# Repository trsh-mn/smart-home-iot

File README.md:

# 스마트홈 IoT 시스템

라즈베리파이 5를 두뇌로, **AI 음성대화봇 · 음악 스피커 · 스마트 전등** 세 기기가 하나의 시스템으로 동작합니다.
무거운 판단(음성인식 · LLM · TTS)은 Pi가, 입출력은 각 기기의 ESP32가 맡도록 역할을 나눴습니다.

## 시스템 구성

```mermaid
flowchart TB
    PI["<b>Raspberry Pi 5</b><br/>Gemini · edge-tts · mosquitto(MQTT)"]
    BOT["<b>AI 음성대화봇</b><br/>ESP32-WROOM-32E"]
    SPK["<b>음악 스피커</b><br/>ESP32-WROOM-32E"]
    LAMP["<b>스마트 전등</b><br/>ESP32-C3"]
    PHONE["휴대폰"]

    BOT -- "UDP 5005 · 마이크 PCM" --> PI
    PI -- "UDP 6000 · 음성 응답 PCM" --> BOT
    PI -- "TCP 6001 · 음악 스트림" --> SPK
    PHONE -. "Bluetooth A2DP" .-> SPK
    PI -- "MQTT · 전원/색상/밝기" --> LAMP
    PI <-- "MQTT · 상태 · 볼륨" --> BOT
    PI <-- "MQTT · 모드 · 볼륨" --> SPK
```

| 데이터 | 방식 | 이유 |
|---|---|---|
| 상태 전환 · 제어 명령 | **MQTT** | 작고 가벼운 메시지 |
| 짧은 음성 (마이크 · 응답) | **UDP** | 지연이 적음 |
| 긴 음악 스트림 | **TCP** | 손실 없이 순서 보장 |

## 폴더 구조

```
firmware/
├── voice_bot/       AI 음성대화봇 (Arduino)
├── music_speaker/   Wi-Fi · Bluetooth 음악 스피커 (Arduino)
└── smart_lamp/      스마트 전등 (ESP-IDF)
server/              라즈베리파이 코드 (Python)
hardware/
├── lamp_v1/         전등 PCB v1 — KiCad 원본, 거버, BOM, CPL
└── lamp_v2/         전등 PCB v2 (진행 중) — KiCad 원본
docs/images/         사진 · 회로도 · PCB 이미지
```

---

## 1. AI 음성대화봇 — `firmware/voice_bot`

- ESP32는 마이크 · 스피커 입출력만, Pi는 음성인식 · LLM · TTS를 담당
- 상태(`idle` · `listening` · `thinking` · `speaking` · `playing_music`)는 MQTT, 음성은 **16-bit / 16kHz mono PCM**을 UDP로 전송
- **RMS 기반 VAD**로 말할 때만 전송. 음악이 재생 중이면 역치를 높여 음악 소리를 무시
- 응답 재생 중(+300ms)에는 녹음하지 않아 자기 목소리를 명령으로 인식하지 않음

| 부품 | 연결 (ESP32 GPIO) |
|---|---|
| INMP441 마이크 (I2S) | SCK 32 · WS 33 · SD 34 |
| MAX98357A 앰프 (I2S) | BCLK 26 · LRC 25 · DIN 22 |
| 스피커 | 8Ω 3W |

## 2. Wi-Fi · Bluetooth 음악 스피커 — `firmware/music_speaker`

- 대화 응답과 음악이 한 스피커에서 충돌하지 않도록 **기기를 분리**
- **Wi-Fi 모드**: Pi의 음악을 TCP로 수신 (44.1kHz 스테레오) / **Bluetooth 모드**: 휴대폰과 직접 연결
- 모드 전환: BOOT 버튼 1초 또는 MQTT `music/mode` ← `bt` / `wifi`

| 부품 | 연결 (ESP32 GPIO) |
|---|---|
| MAX98357A 앰프 (I2S) | BCLK 26 · LRC 25 · DIN 22 |
| 모드 전환 버튼 | BOOT (GPIO 0) |

## 3. 스마트 전등 — `firmware/smart_lamp`

- 18650 배터리로 동작하는 무선 전등. **PCB를 KiCad로 직접 설계**하고 JLCPCB에서 제작
- Arduino → **ESP-IDF**로 이전, MQTT 토픽 세 개로 전원 · 색상 · 밝기 제어
- 제어 함수를 Pi 쪽 `server/lamp/core.py`로 모아 Gemini · 알람 · (향후) 앱이 같은 함수를 호출
- 원하는 시간에 켜고 끄는 알람 예약 (APScheduler, cron 방식)

| 항목 | 내용 |
|---|---|
| MCU | ESP32-C3 |
| LED | WS2812B 30구 · GPIO 4 · RMT 제어 |
| 전원 | 18650 셀 · 5V 부스트 |
| 레벨 시프터 | 74AHCT125 (3.3V → 5V) |

### PCB v1 → v2

| | v1 (제작 완료) | v2 (아트웍 진행 중) |
|---|---|---|
| PCB |  |  |
| MCU | 개발보드를 꽂아서 사용 | ESP32-C3-WROOM-02 모듈 직접 실장 |
| 전원 | 외부 부스트 모듈 사용 | 충전(TP4056) · 부스트(MT3608) · LDO(ME6211) 내장 |
| 레벨 시프터 | 74AHCT125 (4채널) | 74AHCT1G125 (1채널) |
| LED 전원 | 항상 공급 | 로드 스위치(TPS22919)로 펌웨어가 켜고 끔 |
| 펌웨어 업로드 | 개발보드 USB | ESP32-C3 내장 USB (USB-C) |

회로도: [v1](docs/images/lamp_v1_schematic.png) · [v2](docs/images/lamp_v2_schematic.png)

---

## MQTT 토픽

| 토픽 | 값 | 보내는 쪽 → 받는 쪽 |
|---|---|---|
| `lamp/power` | `on` / `off` | Pi → 전등 |
| `lamp/brightness` | `0` ~ `100` | Pi → 전등 |
| `lamp/color` | `[r, g, b]` 또는 `r,g,b` | Pi → 전등 |
| `device/state` | `idle` / `thinking` / `speaking` … | Pi → |
| `music/state` | `playing` / `stopped` | Pi → 음성대화봇 (VAD 역치 조절) |
| `speaker/volume` | `0` ~ `100` | → 음성대화봇 |
| `music/volume` | `0` ~ `100` | → 음악 스피커 |
| `music/mode` | `bt` / `wifi` | → 음악 스피커 |

---

## 트러블슈팅

### 마이크에 잡음만 들어오는 문제 (음성대화봇)
- **문제**: 한 보드에 마이크와 스피커(앰프)를 함께 배선하자 마이크 입력에 "지지직" 잡음만 들어옴
- **확인**: 멀티미터로 각 부품의 전압을 측정하며 하나씩 정상 동작을 확인
- **해결**: 마이크와 스피커(앰프)의 GND 선을 분리해 연결 → 잡음 해결

### Wi-Fi · Bluetooth 동시 사용 시 용량 부족 (음악 스피커)
- **문제**: Wi-Fi와 Bluetooth 오디오를 동시에 쓰기엔 ESP32의 용량이 부족
- **해결**: 두 모드로 나누고, Bluetooth 사용 중에는 Wi-Fi 오디오를 끄도록 전환 설계

### ESP32-C3는 클래식 Bluetooth 미지원 (음악 스피커)
- **문제**: 휴대폰 음악을 받으려면 클래식 Bluetooth(A2DP)가 필요한데 ESP32-C3는 미지원
- **해결**: 클래식 Bluetooth를 지원하는 ESP32-WROOM-32E 선택

### ESP-IDF 전환 후 Wi-Fi 연결 실패 (스마트 전등)
- **문제**: Arduino에서는 잘 되던 Wi-Fi가 ESP-IDF로 옮기자 연결 실패 (인증 타임아웃)
- **확인**: ESP32-C3 저가 보드에서 송신(TX) 출력이 너무 강해 같은 문제가 생기는 사례 확인
- **해결**: 송신 출력을 낮춰 연결 안정화 (34 × 0.25dBm = 8.5dBm)
  ```c
  ESP_ERROR_CHECK(esp_wifi_set_max_tx_power(34));
  ```

---

## 빌드 · 실행

### 공통: 비밀 정보 설정
Wi-Fi · MQTT 계정과 API 키는 GitHub에 올리지 않습니다. 각 폴더의 예시 파일을 복사해 값을 채우세요.

| 위치 | 복사할 파일 → 만들 파일 |
|---|---|
| `firmware/voice_bot/` | `secrets.example.h` → `secrets.h` |
| `firmware/music_speaker/` | `secrets.example.h` → `secrets.h` |
| `firmware/smart_lamp/main/` | `secrets.example.h` → `secrets.h` |
| `server/` | `.env.example` → `.env` |

### 음성대화봇 · 음악 스피커 (Arduino IDE)
- 보드: ESP32-WROOM-32E 개발보드 (**Arduino ESP32 core 3.x**)
- 라이브러리: `PubSubClient`, 음악 스피커는 추가로 `ESP32-A2DP`
- 음악 스피커는 **Tools → Partition Scheme → Huge APP (3MB No OTA)** 필요

### 스마트 전등 (ESP-IDF v5.3.1)
```bash
cd firmware/smart_lamp
idf.py set-target esp32c3
idf.py build flash monitor
```
MQTT 브로커 주소는 `idf.py menuconfig` → **Example Configuration → Broker URL**에서 설정합니다.

### 라즈베리파이 서버 (Python 3.13)
```bash
sudo apt install mosquitto ffmpeg
cd server
python -m venv .venv && source .venv/bin/activate
pip install -r requirements.txt
set -a; source .env; set +a      # .env 의 값을 환경변수로 불러오기
python assistant.py
```
ESP32 기기들의 IP 주소는 `server/audio_client.py` 상단의 `VOICE_IP`, `MUSIC_IP`에 입력합니다.

---

## 앞으로 할 일
- [ ] 전등 PCB v2 아트웍 완료 및 제작
- [ ] 휴대폰 앱에서 전등 제어 (Pi `lamp/core.py` 함수 재사용)

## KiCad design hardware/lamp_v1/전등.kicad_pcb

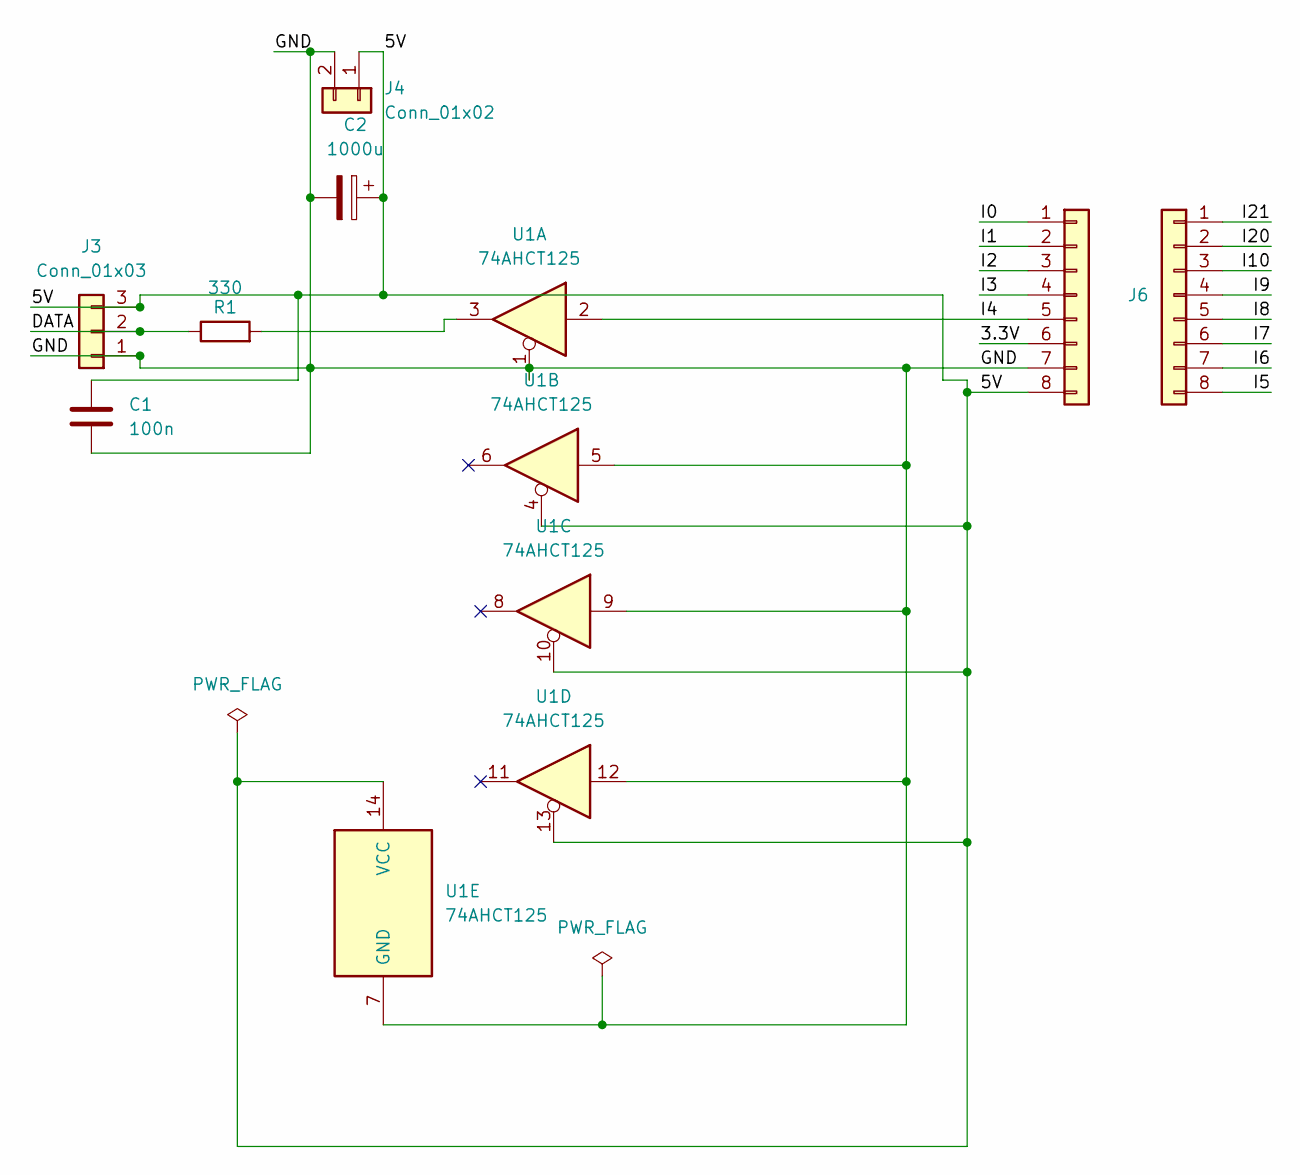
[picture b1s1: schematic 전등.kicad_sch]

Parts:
C1: 100n; C_0805_2012Metric
C2: 1000u; CP_Radial_D8.0mm_P3.50mm
J3: Conn_01x03; PinHeader_1x03_P2.54mm_Vertical
J4: Conn_01x02; PinHeader_1x02_P2.54mm_Vertical
J5, J6: Conn_01x08; PinSocket_1x08_P2.54mm_Vertical
R1: 330; R_0805_2012Metric
U1: 74AHCT125; SOIC-14_3.9x8.7mm_P1.27mm

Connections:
/3.3V: J5.6
/5V: C1.1, C2.1, J3.3, J4.1, J5.8, U1.4, U1.10, U1.13, U1.14 (VCC)
/DATA: J3.2, R1.1
/GND: C1.2, C2.2, J3.1, J4.2, J5.7, U1.1, U1.5, U1.7 (GND), U1.9, U1.12
/I0: J5.1
/I1: J5.2
/I2: J5.3
/I3: J5.4
/I4: J5.5, U1.2
/I5: J6.8
/I6: J6.7
/I7: J6.6
/I8: J6.5
/I9: J6.4
/I10: J6.3
/I20: J6.2
/I21: J6.1
unnamed: R1.2, U1.3

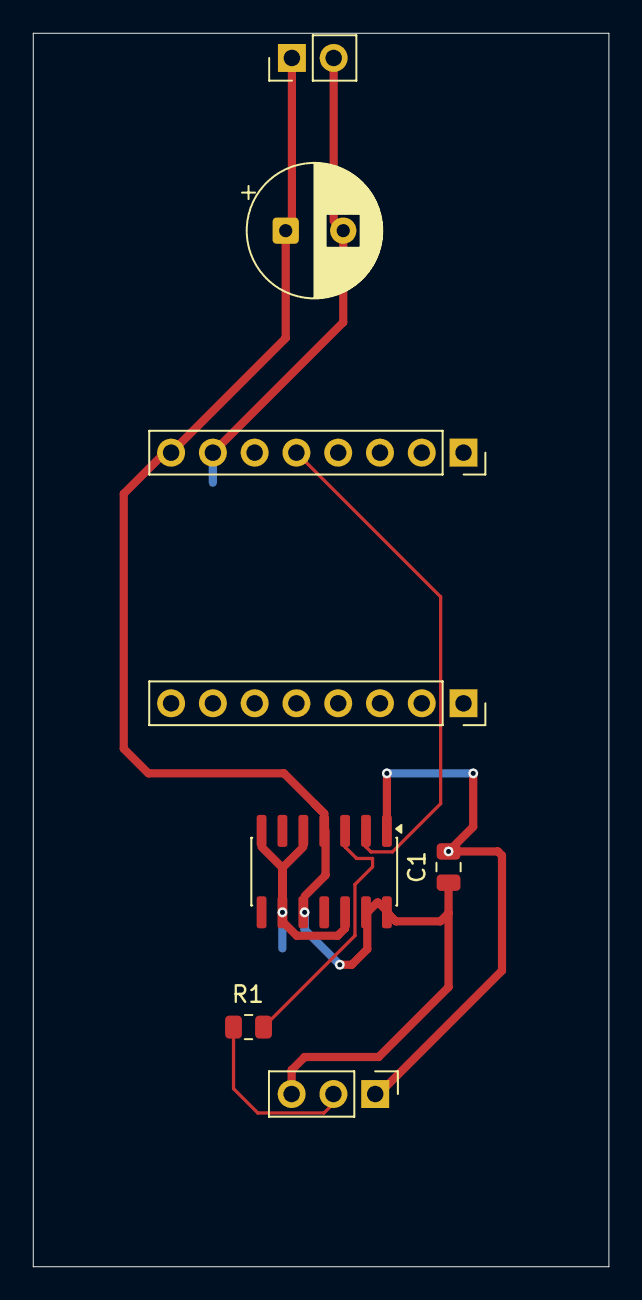
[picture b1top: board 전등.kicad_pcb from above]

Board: 2 copper layers, 35.0 x 75.0 mm, 8 parts (0 on the bottom side), 5 nets.

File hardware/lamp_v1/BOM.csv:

"Comment";"Designator";"Footprint";"";"";"";
100n;"C1";"C_0805_2012Metric";;"";;;
1000u;"C2";"CP_Radial_D8.0mm_P3.50mm";;"";;;
Conn_01x03;"J3";"PinHeader_1x03_P2.54mm_Vertical";;"";;;
Conn_01x02;"J4";"PinHeader_1x02_P2.54mm_Vertical";;"";;;
Conn_01x08;"J5, J6";"PinSocket_1x08_P2.54mm_Vertical";;"";;;
330;"R1";"R_0805_2012Metric";;"";;;
74AHCT125;"U1";"SOIC-14_3.9x8.7mm_P1.27mm";;"";;;

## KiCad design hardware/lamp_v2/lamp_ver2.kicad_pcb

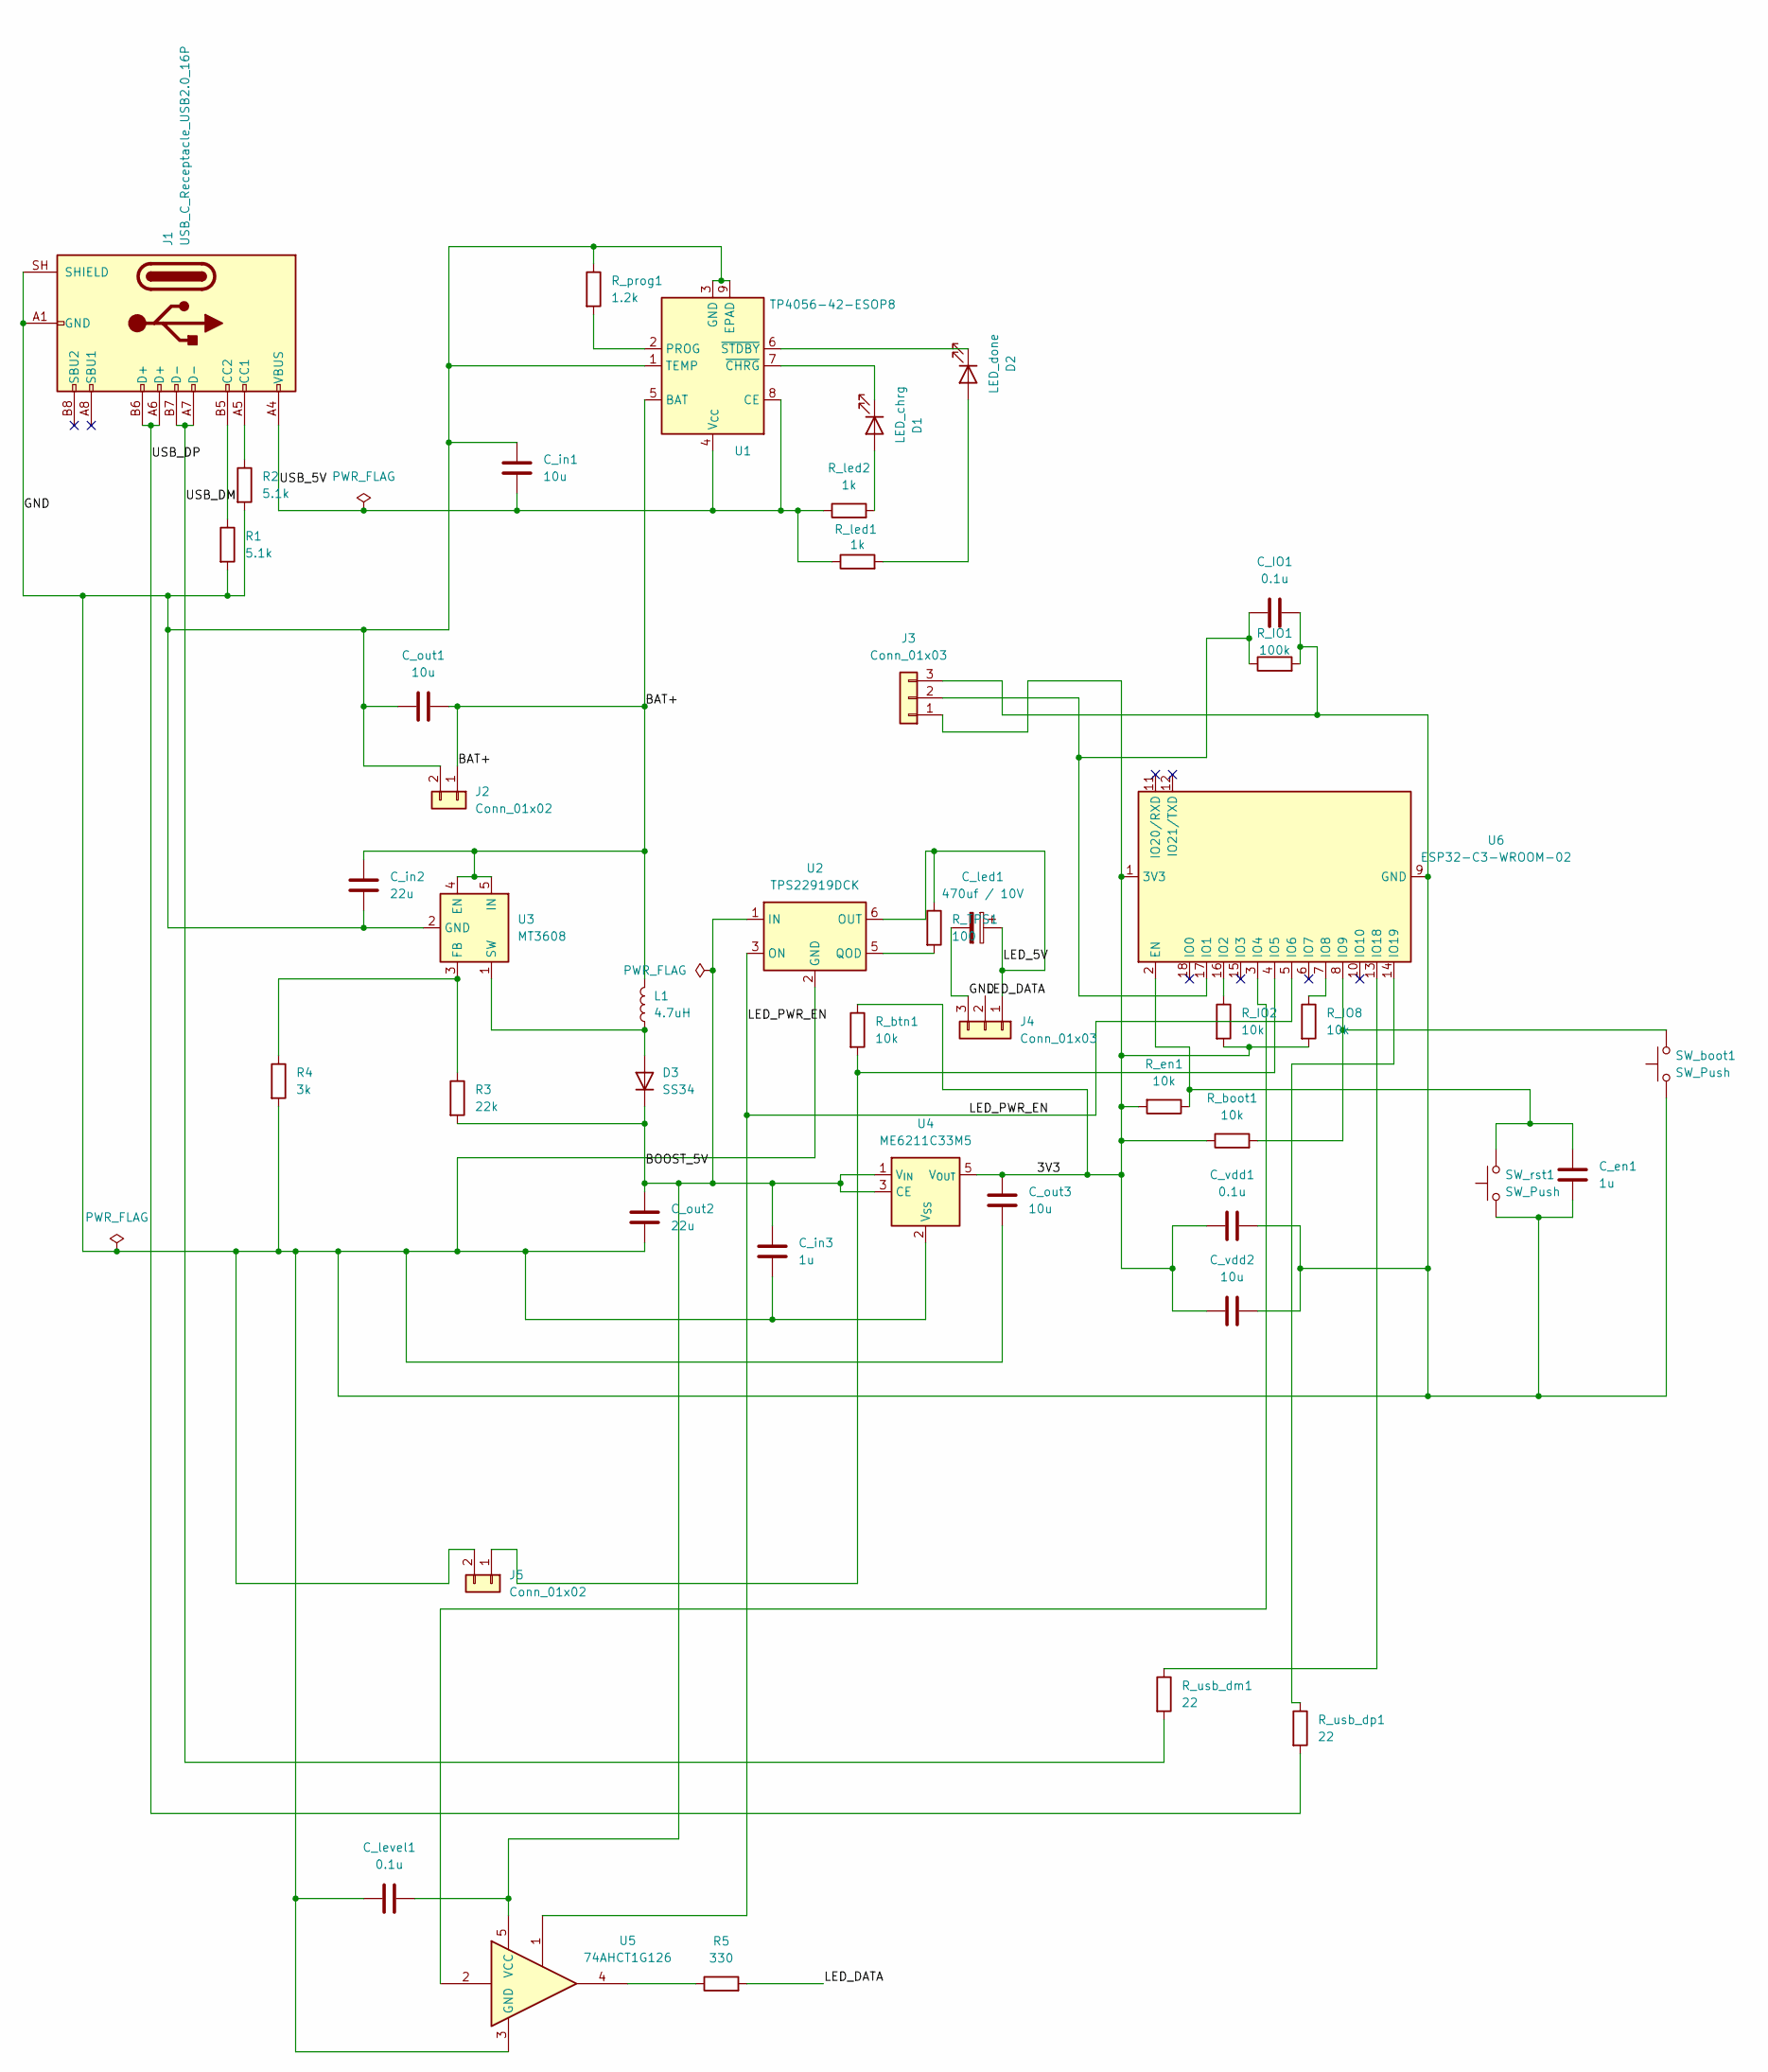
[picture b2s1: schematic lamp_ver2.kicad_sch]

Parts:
C_IO1: 0.1u; C_0603_1608Metric
C_en1: 1u; C_0603_1608Metric
C_in1: 10u; C_0805_2012Metric
C_in2: 22u; C_1206_3216Metric
C_in3: 1u; C_0603_1608Metric
C_led1: 470uf / 10V; CP_Radial_D6.3mm_P2.50mm
C_level1: 0.1u; C_0603_1608Metric
C_out1, C_out3: 10u; C_0805_2012Metric
C_out2: 22u; C_1206_3216Metric
C_vdd1: 0.1u; C_0603_1608Metric
C_vdd2: 10u; C_0805_2012Metric
D1: LED_chrg; LED_0603_1608Metric
D2: LED_done; LED_0603_1608Metric
D3: SS34; D_SMA
J1: USB_C_Receptacle_USB2.0_16P; USB_C_Receptacle_HRO_TYPE-C-31-M-12
J2, J5: Conn_01x02; JST_XH_B2B-XH-A_1x02_P2.50mm_Vertical
J3, J4: Conn_01x03; JST_XH_B3B-XH-A_1x03_P2.50mm_Vertical
L1: 4.7uH; L_Cenker_CKCS5040
R1, R2: 5.1k; R_0603_1608Metric
R3: 22k; R_0603_1608Metric
R4: 3k; R_0603_1608Metric
R5: 330; R_0603_1608Metric
R_IO1: 100k; R_0603_1608Metric
R_IO2, R_IO8: 10k; R_0603_1608Metric
R_TPS1: 100; R_0603_1608Metric
R_boot1: 10k; R_0603_1608Metric
R_btn1: 10k; R_0603_1608Metric
R_en1: 10k; R_0603_1608Metric
R_led1, R_led2: 1k; R_0603_1608Metric
R_prog1: 1.2k; R_0603_1608Metric
R_usb_dm1: 22; R_0603_1608Metric
R_usb_dp1: 22; R_0603_1608Metric
SW_boot1: SW_Push; SW_SPST_SKQG_WithStem
SW_rst1: SW_Push; SW_SPST_SKQG_WithStem
U1: TP4056-42-ESOP8; SOIC-8-1EP_3.9x4.9mm_P1.27mm_EP2.41x3.3mm
U2: TPS22919DCK; SOT-363_SC-70-6
U3: MT3608; SOT-23-6
U4: ME6211C33M5; SOT-23-5
U5: 74AHCT1G126; SOT-23-5
U6: ESP32-C3-WROOM-02

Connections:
/3V3: C_out3.1, C_vdd1.1, C_vdd2.1, J3.1, R_IO2.2, R_IO8.2, R_boot1.1, R_btn1.1, R_en1.2, U4.5 (V_{OUT}), U6.1 (3V3)
/BAT+: C_in2.1, C_out1.2, J2.1, L1.2, U1.5 (BAT), U3.4 (EN), U3.5 (IN)
/BOOST_5V: C_in3.1, C_level1.2, C_out2.2, D3.1 (K), R3.2, U2.1 (IN), U4.1 (V_{IN}), U4.3 (CE), U5.5 (VCC)
/GND: C_IO1.2, C_en1.1, C_in1.2, C_in2.2, C_in3.2, C_led1.2, C_level1.1, C_out1.1, C_out2.1, C_out3.2, C_vdd1.2, C_vdd2.2, J1.A1 (GND), J1.A12 (GND), J1.B1 (GND), J1.B12 (GND), J1.SH (SHIELD), J2.2, J3.3, J4.3, J5.2, R1.2, R2.2, R4.2, R_IO1.2, R_prog1.1, SW_boot1.1, SW_rst1.1, U1.1 (TEMP), U1.3 (GND), U1.9 (EPAD), U2.2 (GND), U3.2 (GND), U4.2 (V_{SS}), U5.3 (GND), U6.9 (GND), U6.19 (GND)
/LED_5V: C_led1.1, J4.1, R_TPS1.1, U2.6 (OUT)
/LED_DATA: J4.2, R5.2
/LED_PWR_EN: U2.3 (ON), U5.1, U6.5 (IO6)
/USB_5V: C_in1.1, J1.A4 (VBUS), J1.A9 (VBUS), J1.B4 (VBUS), J1.B9 (VBUS), R_led1.1, R_led2.1, U1.4 (V_{CC}), U1.8 (CE)
/USB_DM: J1.A7 (D-), J1.B7 (D-), R_usb_dm1.2
/USB_DP: J1.A6 (D+), J1.B6 (D+), R_usb_dp1.2
unnamed: D1.2 (A), R_led2.2
unnamed: D1.1 (K), U1.7 (~CHRG)
unnamed: D2.2 (A), R_led1.2
unnamed: D2.1 (K), U1.6 (~STDBY)
unnamed: D3.2 (A), L1.1, U3.1 (SW)
unnamed: J1.A5 (CC1), R2.1
unnamed: J1.B5 (CC2), R1.1
unnamed: C_IO1.1, J3.2, R_IO1.1, U6.17 (IO1)
unnamed: J5.1, R_btn1.2, U6.4 (IO5)
unnamed: R5.1, U5.4
unnamed: R_prog1.2, U1.2 (PROG)
unnamed: R_TPS1.2, U2.5 (QOD)
unnamed: R3.1, R4.1, U3.3 (FB)
unnamed: C_en1.2, R_en1.1, SW_rst1.2, U6.2 (EN)
unnamed: R_IO2.1, U6.16 (IO2)
unnamed: U5.2, U6.3 (IO4)
unnamed: R_IO8.1, U6.7 (IO8)
unnamed: R_boot1.2, SW_boot1.2, U6.8 (IO9)
unnamed: R_usb_dm1.1, U6.13 (IO18)
unnamed: R_usb_dp1.1, U6.14 (IO19)

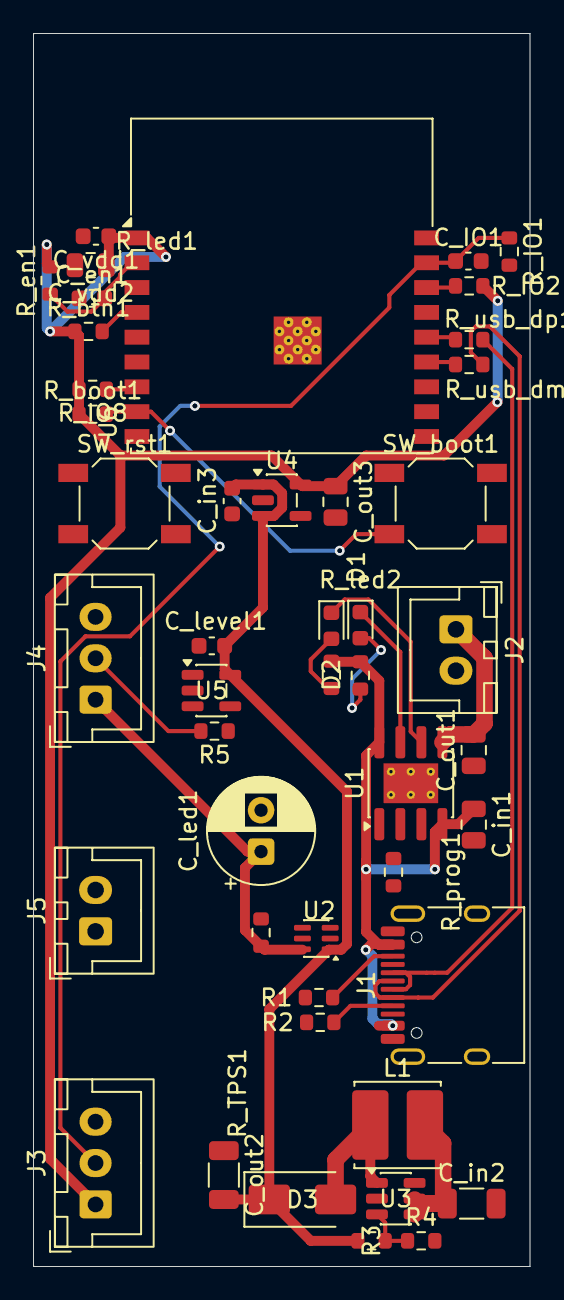
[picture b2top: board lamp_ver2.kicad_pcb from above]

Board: 2 copper layers, 30.0 x 74.5 mm, 46 parts (0 on the bottom side), 30 nets.
